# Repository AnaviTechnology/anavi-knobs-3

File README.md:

# ANAVI Knobs 3

**Open source programmable keypad with 3 rotary encoders**

ANAVI Knobs 3 offers three rotary encoders with clickable switches and a RGB LED. The black, gold-plated PCB also features an I²C slot for adding peripherals such as a mini OLED display. Each rotary encoder is also a key and can be reprogrammed to activate a macro or even a dedicated shortcut.

ANAVI Knobs 3 has been designed with [the cross platform and open source electronics design automation suite KiCad](https://kicad-pcb.org/).

[ANAVI Knobs 3, ANAVI Knob 1 and ANAVI Macro Pad 10 were brought to market through a crowdfunding campaign at Crowd Supply](https://www.crowdsupply.com/anavi-technology/anavi-macro-pad-10). For more details please visit https://anavi.technology/

# License

The project is released under the [Creative Commons Attribution-ShareAlike 4.0 International (CC BY-SA 4.0)](https://creativecommons.org/licenses/by-sa/4.0/).

Note: This is a human-readable summary of (and not a substitute for) the [license](https://creativecommons.org/licenses/by-sa/4.0/legalcode).

You are free to:

Share — copy and redistribute the material in any medium or format Adapt — remix, transform, and build upon the material for any purpose, even commercially. The licensor cannot revoke these freedoms as long as you follow the license terms. Under the following terms:

Attribution — You must give appropriate credit, provide a link to the license, and indicate if changes were made. You may do so in any reasonable manner, but not in any way that suggests the licensor endorses you or your use. ShareAlike — If you remix, transform, or build upon the material, you must distribute your contributions under the same license as the original. No additional restrictions — You may not apply legal terms or technological measures that legally restrict others from doing anything the license permits. Notices:

You do not have to comply with the license for elements of the material in the public domain or where your use is permitted by an applicable exception or limitation. No warranties are given. The license may not give you all of the permissions necessary for your intended use. For example, other rights such as publicity, privacy, or moral rights may limit how you use the material.

You will have to provide a link to the original creator of the project http://www.anavi.technology on any documentation or website.

Credit can be attributed through a link to the creator website: http://www.anavi.technology

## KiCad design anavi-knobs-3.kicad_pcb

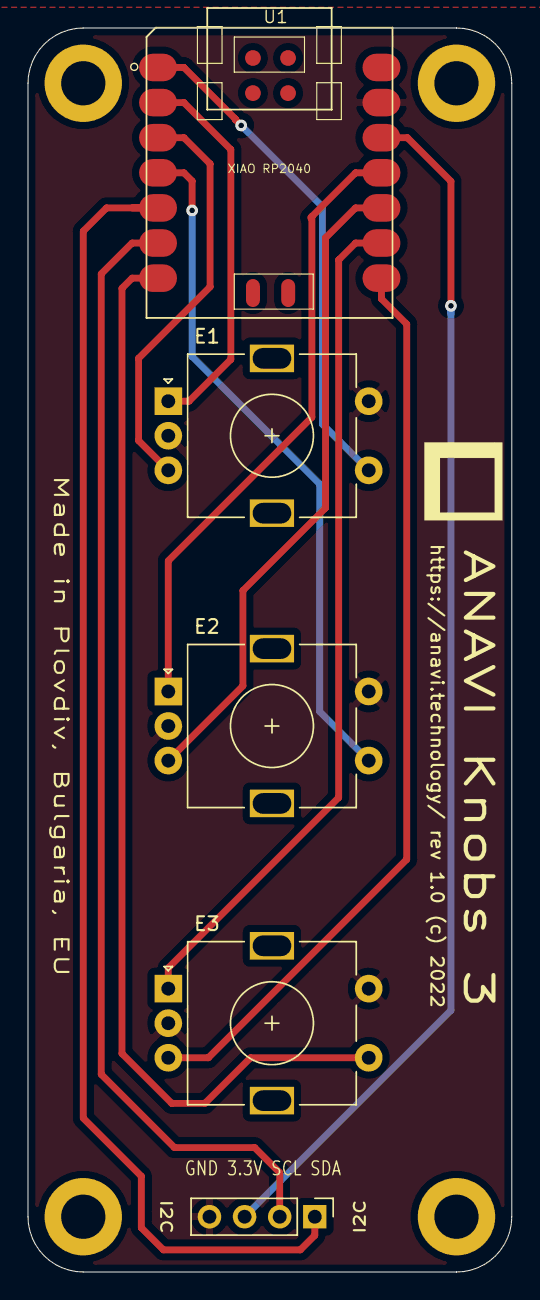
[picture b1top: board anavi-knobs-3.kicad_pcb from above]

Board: 2 copper layers, 35.0 x 90.0 mm, 5 parts (0 on the bottom side), 13 nets.

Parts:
E1, E2, E3: Rotary_Encoder_Switch; RotaryEncoder_Alps_EC11E-Switch_Vertical_H20mm
I2C: Conn_01x04_Female; PinHeader_1x04_P2.54mm_Vertical
U1: XIAO RP2040; Seeeduino XIAO-MOUDLE14P-2.54-21X17.8MM

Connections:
+3V3: I2C.3, U1.12
GND: E1.C, E1.S2, E2.C, E2.S2, E3.C, E3.S2, I2C.4, U1.13
unnamed: E1.A, U1.2
unnamed: E1.B, U1.3
unnamed: E1.S1, U1.1
unnamed: E2.A, U1.11
unnamed: E2.B, U1.10
unnamed: E2.S1, U1.4
unnamed: E3.A, U1.9
unnamed: E3.B, U1.8
unnamed: E3.S1, U1.7
unnamed: I2C.1, U1.5
unnamed: I2C.2, U1.6

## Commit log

2022-04-25 Initial commit
    Initial commit for ANAVI Knobs 3.
2022-06-28 anavi-knobs-3.kicad_pcb: Draw enclosure
    Draw enclosure on the fabrication layer.
2022-11-05 README.md: Add images and more details
    Add a couple of images and more details about the project.

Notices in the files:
anavi-knobs-3.kicad_pcb:
https://anavi.technology/ rev 1.0 (c) 2022
